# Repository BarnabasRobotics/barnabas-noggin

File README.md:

# barnabas-noggin
Controller board for Barnabas-Bot.  Arduino-Uno compatible board.  

Versions:
 
 Using Nano plug-in board
 - V3: Rev 2C 
 - V3.1: Rev 2D, Rev 2E
 
 No nano plug-in board
 - V4: Rev 3A, 3B 

Changes in Rev2D:
 - Remove 5V regulator
 - Add fuse protection on 5V and 3.3V
 - Add DC Driver Controller
 - Fix silkscreen text

Changes in Rev2E:
 - Silkscreen updates

[AutoDesk Fusion 360 file](https://a360.co/3gs5b8a)

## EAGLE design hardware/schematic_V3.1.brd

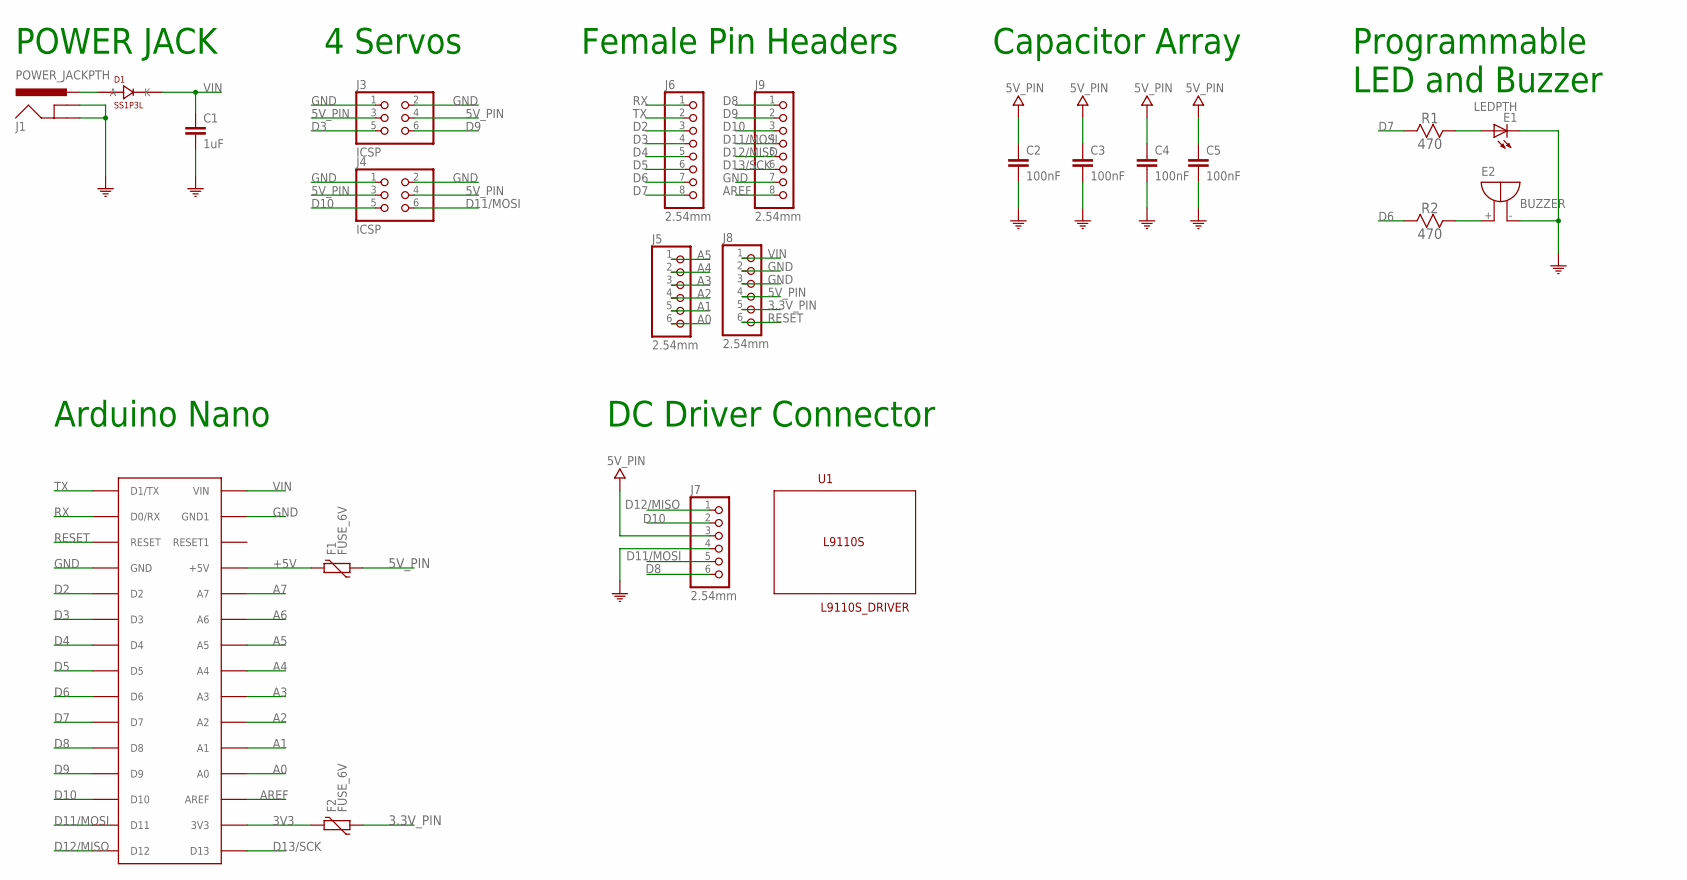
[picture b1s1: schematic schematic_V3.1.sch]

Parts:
C1: 1uF; C0603-ROUND; PARTNO CC0603KRX5R8BB105
C2, C3, C4, C5: 100nF; C0603-ROUND; PARTNO CC0603ZRY5V9BB104
D1: SS1P3L; DIODI_DO220AAL; PARTNO SS1P3L-M3/84A
E1: LEDPTH; LED5MM
E2: BUZZER
F1, F2: FUSE_6V; FUSE_0603; PARTNO MF-FSMF050X-2
J1: POWER_JACKPTH; POWER_JACK_PTH; PARTNO EJ508A
J3, J4: ICSP; CONNECTOR_2X3; PARTNO M20-9980346
J5, J7, J8: 2.54mm; 1X06; PARTNO M20-7820646
J6, J9: 2.54mm; 1X08; PARTNO PPTC081LFBN-RC
R1, R2: 470; RESISTOR_PTH
U1: L9110S_DRIVER
U$1: ARDUINONANO; PDIP-32

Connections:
3.3V_PIN: F2.1, J8.5
3V3: F2.2, U$1.3V3
5V_PIN: C2.1, C3.1, C4.1, C5.1, F1.1, J3.3, J3.4, J4.3, J4.4, J7.3, J8.4
+5V: F1.2, U$1.+5V
A0: J5.6, U$1.A7 (A0)
A1: J5.5, U$1.A6 (A1)
A2: J5.4, U$1.A5 (A2)
A3: J5.3, U$1.A4 (A3)
A4: J5.2, U$1.A3 (A4)
A5: J5.1, U$1.A2 (A5)
A6: U$1.A1 (A6)
A7: U$1.A0 (A7)
AREF: J9.8, U$1.AREF
D2: J6.3, U$1.D2
D3: J3.5, J6.4, U$1.D3
D4: J6.5, U$1.D4
D5: J6.6, U$1.D5
D6: J6.7, R2.1, U$1.D6
D7: J6.8, R1.1, U$1.D7
D8: J7.6, J9.1, U$1.D8
D9: J3.6, J9.2, U$1.D9
D10: J4.5, J7.2, J9.3, U$1.D10
D11/MOSI: J4.6, J7.5, J9.4, U$1.D11
D12/MISO: J7.1, J9.5, U$1.D12
D13/SCK: J9.6, U$1.D13
GND: C1.2, C2.2, C3.2, C4.2, C5.2, E1.K (C), E2.-, J1.GND, J1.GNDBREAK, J3.1, J3.2, J4.1, J4.2, J7.4, J8.2, J8.3, J9.7, U$1.GND, U$1.GND1
unnamed: D1.P$2 (A), J1.PWR
unnamed: E1.A, R1.2
unnamed: E2.+, R2.2
RESET: J8.6, U$1.RESET
RX: J6.1, U$1.D0/RX
TX: J6.2, U$1.D1/TX
VIN: C1.1, D1.P$1 (K), J8.1, U$1.VIN

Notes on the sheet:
Arduino Nano
POWER JACK
4 Servos
Female Pin Headers
Programmable LED and Buzzer
Capacitor Array
DC Driver Connector

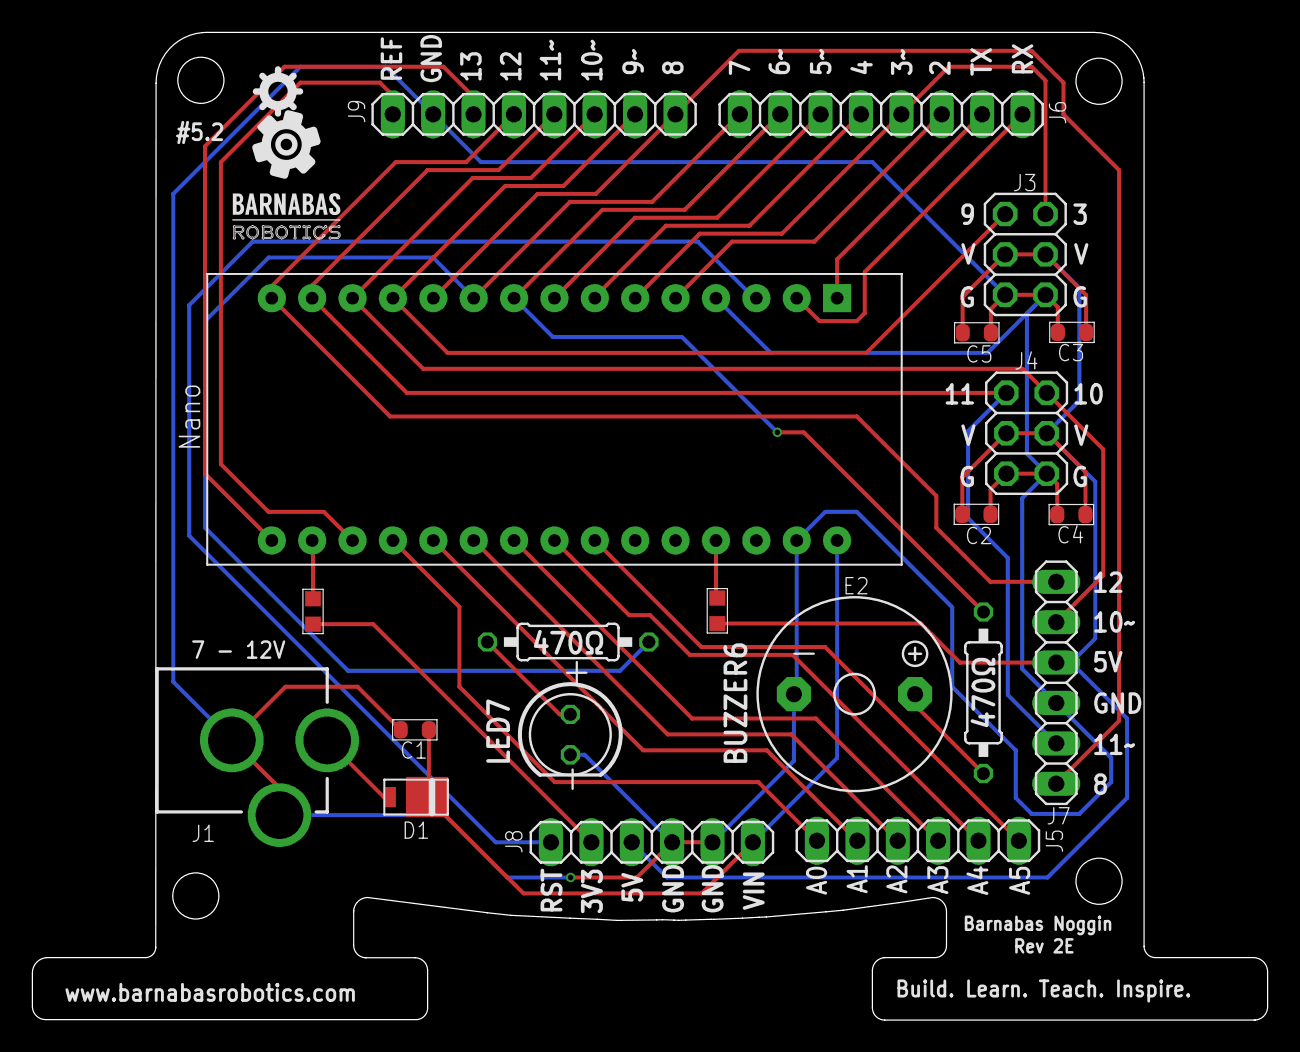
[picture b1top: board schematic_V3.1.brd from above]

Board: 2 copper layers, 77.7 x 62.1 mm, 22 parts (0 on the bottom side), 31 nets.

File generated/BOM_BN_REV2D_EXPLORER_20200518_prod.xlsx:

ITEM | PART ID | VALUE | PACKAGE | SPECIFICATION | QTY | NOTES | BRAND | DIGIKEY PART # | MFG PART # | Notes
1 | C1 | 1uF | 603 | C0603-ROUND | 1 |  | Yageo | 311-1445-2-ND | CC0603KRX5R8BB105
2 | J5, J7, J8 | 2.54mm | Thru-Hole | 2.54 mm female 1 x 6 | 3 |  | Harwin Inc. | 952-1809-ND | M20-7820646
3 | J6, J9 | 2.54mm | Thru-Hole | 2.54 mm female 1 x 8 | 2 |  | Sullins Connector Solutions | S7006-ND | PPTC081LFBN-RC
4 | R1 | 4.7K | Thru-Hole | RESISTOR_PTH | 1 | NO PLACE | * | * | * | NO PLACE
5 | C2, C3, C4, C5 | 100nF | 603 | C0603-ROUND | 4 |  | Yageo | 311-1343-2-ND | CC0603ZRY5V9BB104
6 | R2 | 470 | Thru-Hole | RESISTOR_PTH | 1 | NO PLACE | * | * | * | NO PLACE
7 | Nano | 2.54mm | Thru-Hole | 2.54 mm female 1 x 15 | 2 |  | Sullins Connector Solutions | S7013-ND | ber PPTC151LFBN-RC
8 | E2 | BUZZER | Thru-Hole | 5V Passive buzzer | 1 | NO PLACE | * | * | * | NO PLACE
9 | F1, F2 | FUSE_6V | 603 | FUSE_0603 | 2 |  | Bourns Inc. | MF-FSMF050X-2CT-ND | MF-FSMF050X-2
10 | J3, J4 | 2.54mm | Thru-Hole | 2.54 mm header 2 x 3 | 2 |  | Harwin Inc. | 952-2121-ND | M20-9980346
11 | E1 | 5mm | Thru-Hole | LED5MM | 1 | NO PLACE | * | * | * | NO PLACE
12 | J1 | POWER_JACKPTH | Thru-Hole | POWER_JACK_PTH | 1 |  | MPD (Memory Protection Devices) | EJ508A-ND | EJ508A
13 | D1 | SS1P3L | DO-220AA | DIODI_DO220AAL | 1 |  | Vishay Semiconductor Diodes Division | SS1P3L-M3/84AGITR-ND | SS1P3L-M3/84A
 |  |  |  | Total Thru Hole | 14
 |  |  |  | Total SMD | 8
 |  |  |  | Total parts | 22

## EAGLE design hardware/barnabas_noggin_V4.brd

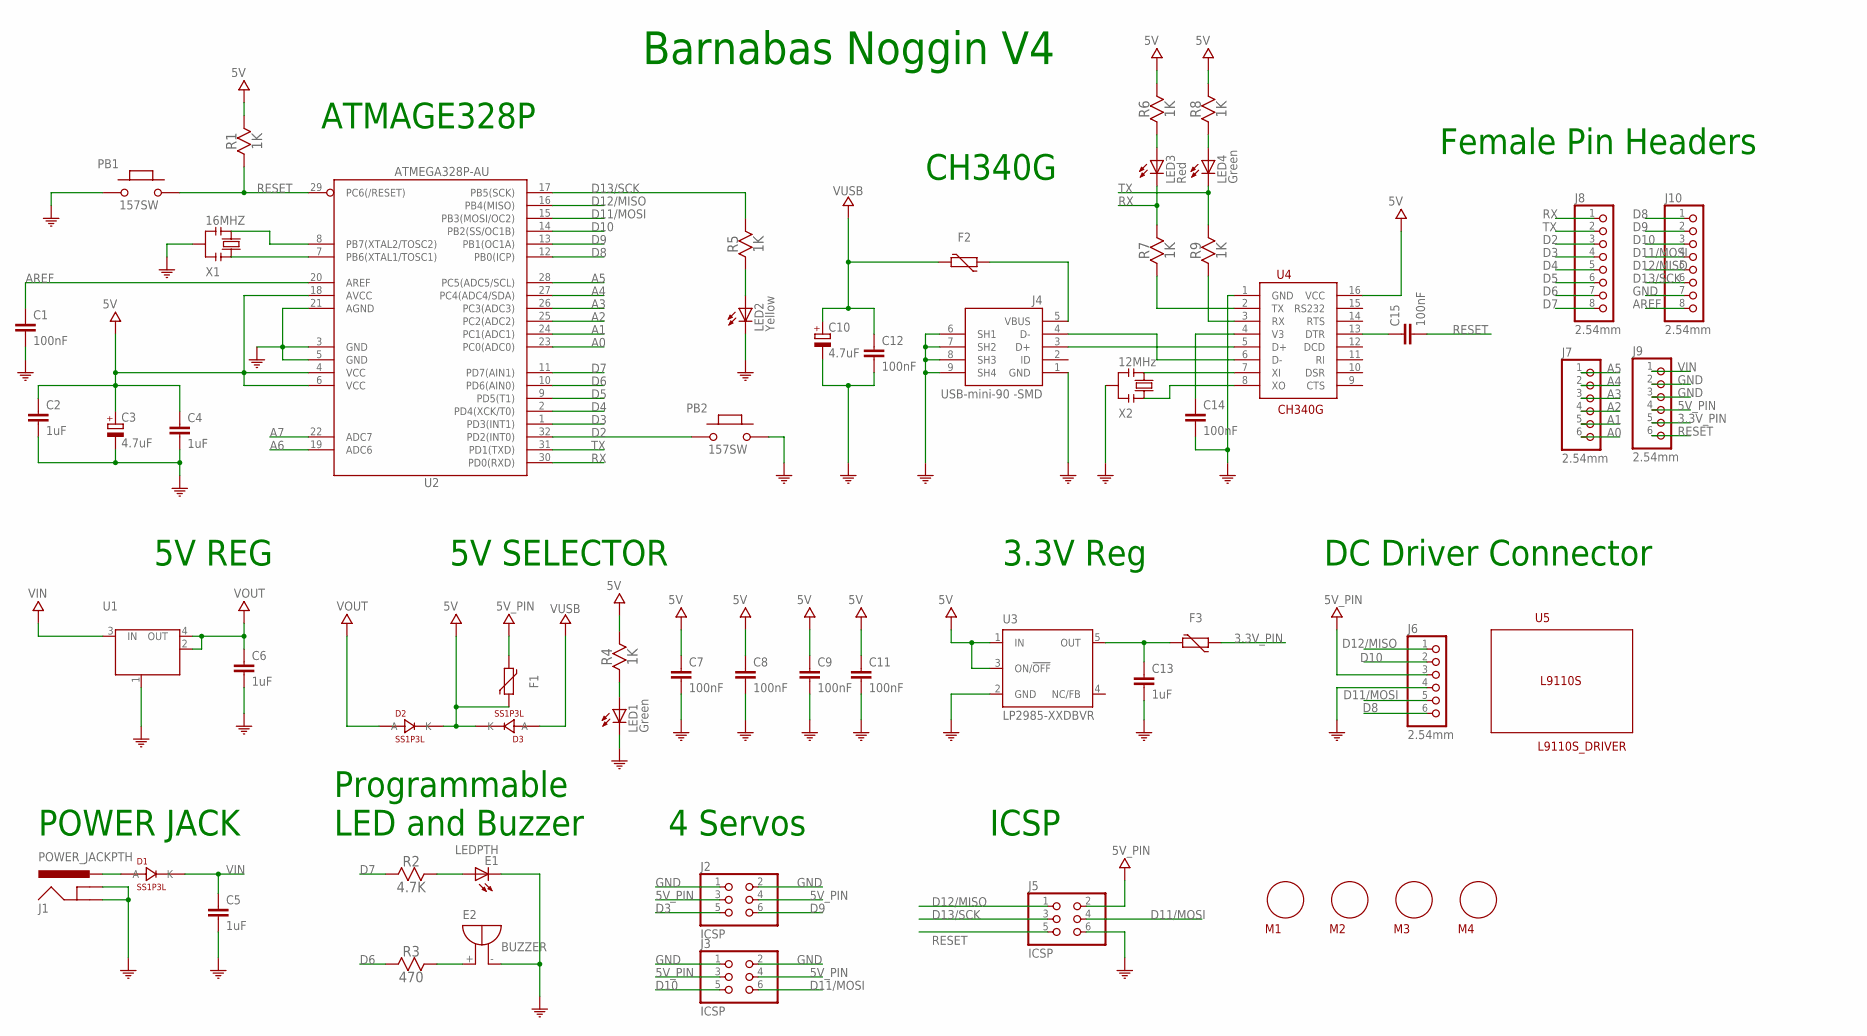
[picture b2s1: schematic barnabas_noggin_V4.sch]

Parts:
C1, C7, C8, C9, C11, C12, C14, C15: 100nF; C0603-ROUND; PARTNO CC0603ZRY5V9BB104
C2, C4, C5, C6, C13: 1uF; C0603-ROUND; PARTNO CC0603KRX5R8BB105
C3, C10: 4.7uF; TAN-A; PARTNO CL31A475KOHNNNE
D1, D2, D3: SS1P3L; DIODI_DO220AAL; PARTNO SS1P3L-M3/84A
E1: LEDPTH; LED5MM
E2: BUZZER
F1, F2, F3: FUSE_6V; FUSE_0603; PARTNO MF-FSMF050X-2
J1: POWER_JACKPTH; POWER_JACK_PTH; PARTNO EJ508A
J2, J3, J5: ICSP; CONNECTOR_2X3; PARTNO M20-9980346
J4: USB-mini-90 -SMD; CONNECTOR_USB_MINI-B; PARTNO UJ2-MBH-1-SMT-TR
J6, J7, J9: 2.54mm; 1X06; PARTNO M20-7820646
J8, J10: 2.54mm; 1X08; PARTNO PPTC081LFBN-RC
LED1, LED4: Green; LED_0805; PARTNO LTST-C171GKT
LED2: Yellow; LED_0805; PARTNO LTST-C171KSKT
LED3: Red; LED_0805; PARTNO LTST-C170KRKT
M1, M2, M3, M4: MOUNT_HOLE
PB1, PB2: 157SW; SWITCHES_SMD_157SW; PARTNO PTS820 J15M SMTR LFS
R1, R4, R5, R6, R7, R8, R9: 1K; R0603; PARTNO RC0603FR-071KL
R2: 4.7K; RESISTOR_PTH
R3: 470; RESISTOR_PTH
U1: LM1117IMPX-5.0; LM1117_SOT223; PARTNO LM1117IMPX-5.0/NOPB
U2: ATMEGA328P-AU; TQFP32-08; PARTNO ATMEGA328P-AU
U3: LP2985-XXDBVR; SOT23-DBV; PARTNO LP2985-33DBVR
U4: CH340G; SOIC16
U5: L9110S_DRIVER
X1: 16MHZ; CRYSTAL; PARTNO CSTNE16M0V530000R0
X2: 12MHz; CRYSTAL; PARTNO CSTNE12M0G550000R0

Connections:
3.3V: C13.1, F3.2, U3.5 (OUT)
3.3V_PIN: F3.1, J9.5
5V: C2.1, C3.1 (+), C4.1, C7.1, C8.1, C9.1, C11.1, D2.P$1 (K), D3.P$1 (K), F1.1, R1.2, R4.2, R6.2, R8.2, U2.4 (VCC), U2.6 (VCC), U2.18 (AVCC), U3.1 (IN), U3.3 (ON/!OFF), U4.16 (VCC)
5V_PIN: F1.2, J2.3, J2.4, J3.3, J3.4, J5.2, J6.3, J9.4
A0: J7.6, U2.23 (PC0(ADC0))
A1: J7.5, U2.24 (PC1(ADC1))
A2: J7.4, U2.25 (PC2(ADC2))
A3: J7.3, U2.26 (PC3(ADC3))
A4: J7.2, U2.27 (PC4(ADC4/SDA))
A5: J7.1, U2.28 (PC5(ADC5/SCL))
A6: U2.19 (ADC6)
A7: U2.22 (ADC7)
AREF: C1.1, J10.8, U2.20 (AREF)
D2: J8.3, PB2.1, U2.32 (PD2(INT0))
D3: J2.5, J8.4, U2.1 (PD3(INT1))
D4: J8.5, U2.2 (PD4(XCK/T0))
D5: J8.6, U2.9 (PD5(T1))
D6: J8.7, R3.1, U2.10 (PD6(AIN0))
D7: J8.8, R2.1, U2.11 (PD7(AIN1))
D8: J6.6, J10.1, U2.12 (PB0(ICP))
D9: J2.6, J10.2, U2.13 (PB1(OC1A))
D10: J3.5, J6.2, J10.3, U2.14 (PB2(SS/OC1B))
D11/MOSI: J3.6, J5.4, J6.5, J10.4, U2.15 (PB3(MOSI/OC2))
D12/MISO: J5.1, J6.1, J10.5, U2.16 (PB4(MISO))
D13/SCK: J5.3, J10.6, R5.2, U2.17 (PB5(SCK))
GND: C1.2, C2.2, C3.2 (-), C4.2, C5.2, C6.2, C7.2, C8.2, C9.2, C10.2 (-), C11.2, C12.2, C13.2, C14.2, E1.K (C), E2.-, J1.GND, J1.GNDBREAK, J2.1, J2.2, J3.1, J3.2, J4.1 (GND), J4.6 (SH1), J4.7 (SH2), J4.8 (SH3), J4.9 (SH4), J5.6, J6.4, J9.2, J9.3, J10.7, LED1.C, LED2.C, PB1.1, PB2.2, U1.1 (GND/ADJ), U2.3 (GND), U2.5 (GND), U2.21 (AGND), U3.2 (GND), U4.1 (GND), X1.2, X2.2
unnamed: U2.8 (PB7(XTAL2/TOSC2)), X1.3
unnamed: U2.7 (PB6(XTAL1/TOSC1)), X1.1
unnamed: LED1.A, R4.1
unnamed: C15.1, U4.13 (DTR)
unnamed: U4.7 (XI), X2.3
unnamed: R7.1, U4.2 (TX)
unnamed: LED3.A, R6.1
unnamed: R9.1, U4.3 (RX)
unnamed: LED4.A, R8.1
unnamed: LED2.A, R5.1
unnamed: C14.1, U4.4 (V3)
unnamed: U4.8 (XO), X2.1
unnamed: J4.3 (D+), U4.5 (D+)
unnamed: J4.4 (D-), U4.6 (D-)
unnamed: D1.P$2 (A), J1.PWR
unnamed: F2.1, J4.5 (VBUS)
unnamed: E1.A, R2.2
unnamed: E2.+, R3.2
RESET: C15.2, J5.5, J9.6, PB1.2, R1.1, U2.29 (PC6(/RESET))
RX: J8.1, LED3.C, R7.2, U2.30 (PD0(RXD))
TX: J8.2, LED4.C, R9.2, U2.31 (PD1(TXD))
VIN: C5.1, D1.P$1 (K), J9.1, U1.3 (IN)
VOUT: C6.1, D2.P$2 (A), U1.2 (OUT), U1.4 (OUT)
VUSB: C10.1 (+), C12.1, D3.P$2 (A), F2.2

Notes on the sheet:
Barnabas Noggin V4
5V REG
ICSP
5V SELECTOR
ATMAGE328P
CH340G
POWER JACK
Programmable LED and Buzzer
4 Servos
Female Pin Headers
DC Driver Connector
3.3V Reg

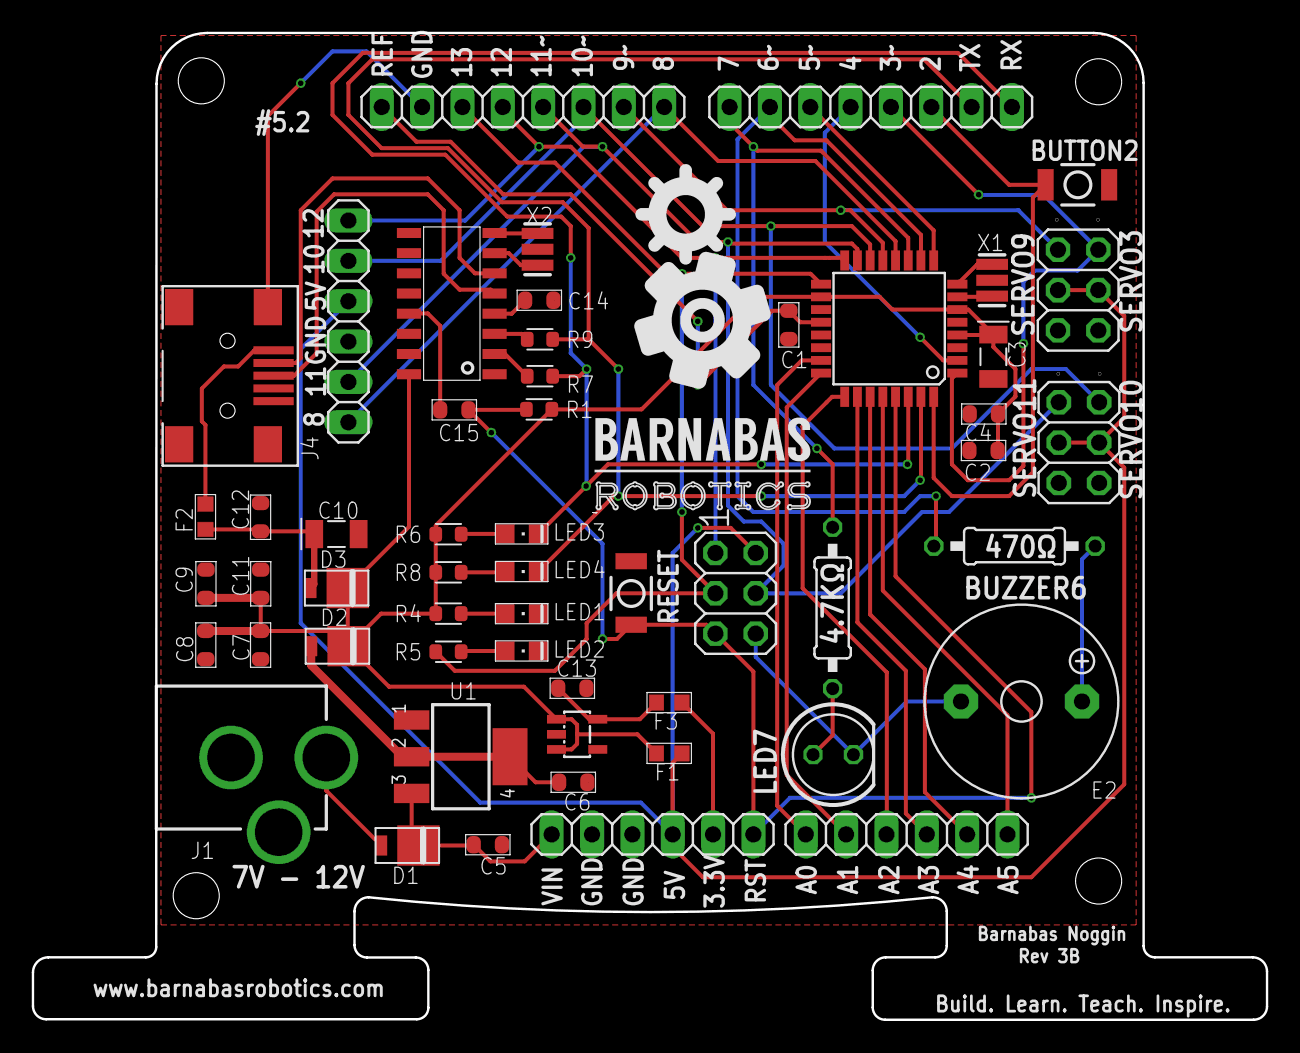
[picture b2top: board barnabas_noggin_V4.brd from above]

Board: 2 copper layers, 77.7 x 62.1 mm, 60 parts (1 on the bottom side), 48 nets.

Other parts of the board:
U$14: BARNABAS_LOGO

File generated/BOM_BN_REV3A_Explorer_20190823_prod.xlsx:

ITEM | PART ID | VALUE | PACKAGE | SPECIFICATION | QTY | NOTES | BRAND | DIGIKEY PART # | MFG PART # | Notes | Other Source
1 | R1, R4, R5, R6, R7, R8, R9 | 1K | 603 | RES SMD 1K OHM 1% 1/10W 0603 | 7 |  | Yageo | 311-1.00KHRTR-ND | RC0603FR-071KL
2 | C2, C4, C5, C6, C13 | 1uF | 603 | CAP CER 1UF 25V X5R 0603 | 5 |  | Yageo | 311-1445-2-ND | CC0603KRX5R8BB105
3 | J6, J7, J9 | 2.54mm | Thru-Hole | CONN RCPT 6POS 0.1 TIN PCB | 3 |  | Harwin Inc. | 952-1809-ND | M20-7820646
4 | J8, J10 | 2.54mm | Thru-Hole | CONN HDR 8POS 0.1 TIN PCB | 2 |  | Sullins Connector Solutions | S7006-ND | PPTC081LFBN-RC
5 | R2 | 4.7K | Thru-Hole | Thru-Hole Resistor | 1 | No Place | * | * | * | No Place
6 | C3, C10 | 4.7uF | 1206 | CAP CER 4.7UF 16V X5R 1206 | 2 |  | Samsung Electro-Mechanics | 1276-3059-2-ND | CL31A475KOHNNNE
7 | X2 | 12MHz | 3-SMD | CER RES 12.0000MHZ 33PF SMD | 1 |  | Murata Electronics North America | 490-17943-2-ND | CSTNE12M0G550000R0
8 | X1 | 16MHZ | 3-SMD | CER RES 16.0000MHZ 15PF SMD | 1 |  | Murata Electronics North America | 490-17948-2-ND | CSTNE16M0V530000R0
9 | C1, C7, C8, C9, C11, C12, C14, C15 | 100nF | 603 | CAP CER 0.1UF 50V Y5V 0603 | 8 |  | Yageo | 311-1343-2-ND | CC0603ZRY5V9BB104
10 | PB1, PB2 | 157SW | * | SWITCH TACTILE SPST-NO 0.05A 12V | 2 |  | C&K | CKN10506TR-ND | PTS820 J15M SMTR LFS
11 | R3 | 470 | Thru-Hole | Thru-Hole Resistor | 1 | No Place | * | * | * | No Place
12 | U2 | ATMEGA328P-32MUR | 32-VQFN (5x5) | IC MCU 8BIT 32KB FLASH 32VQFN | 1 |  | Microchip Technology | ATMEGA328P-MURCT-ND | ATMEGA328P-MUR
13 | E2 | BUZZER | Thru-Hole | 5V Passive Buzzer | 1 | No Place | * | * | * | No Place
14 | U4 | CH340G | * | CH340G | 1 |  | * | * | * |  | https://www.alibaba.com/product-detail/Electronic-Components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
15 | F1, F2, F3 | FUSE_6V | 603 | PTC RESET FUSE 6V 500MA 0603 | 3 |  | Bourns Inc. | MF-FSMF050X-2CT-ND | MF-FSMF050X-2
16 | LED1, LED4 | Green | 805 | LED GREEN CLEAR CHIP SMD | 2 |  | Lite-On Inc. | 160-1423-2-ND | LTST-C171GKT
17 | J2, J3, J5 | ICSP | Thru-Hole | CONN HEADER VERT 6POS 2.54MM | 3 |  | Harwin Inc. | 952-2121-ND | M20-9980346
18 | U5 | L9110S_DRIVER | * | DC Motor Driver | 1 | No Place | * | * | * | No Place
19 | E1 | LEDPTH | Thru-Hole | Thru-Hole 3V LED | 1 | No Place | * | * | * | No Place
20 | U1 | LM1117IMPX-5.0 | SOT-223-4 | IC REG LINEAR 5V 800MA SOT223-4 | 1 |  | Texas Instruments | LM1117IMPX-5.0/NOPBTR-ND | LM1117IMPX-5.0/NOPB
21 | U3 | LP2985-XXDBVR | SOT-23-5 | IC REG LINEAR 3.3V 150MA SOT23-5 | 1 |  | Texas Instruments | 296-18476-2-ND | LP2985-33DBVR
22 | J1 | POWER_JACKPTH | Thru-Hole | CONN PWR JACK 2.1X5.5MM SOLDER | 1 |  | MPD (Memory Protection Devices) | EJ508A-ND | EJ508A
23 | LED3 | Red | 805 | LED RED CLEAR SMD | 1 |  | Lite-On Inc. | 160-1415-2-ND | LTST-C170KRKT
24 | D1, D2, D3 | SS1P3L | DO-220AA | DIODE SCHOTTKY 30V 1.5A DO220AA | 3 |  | Vishay Semiconductor Diodes Division | SS1P3L-M3/84AGITR-ND | SS1P3L-M3/84A
25 | J4 | USB-mini-90 -SMD | * | CONN RCPT USB2.0 MINI B SMD R/A | 1 |  | CUI Inc. | 102-4003-2-ND | UJ2-MBH-1-SMT-TR
26 | LED2 | Yellow | 805 | LED YELLOW CLEAR CHIP SMD | 1 |  | Lite-On Inc. | 160-1428-2-ND | LTST-C171KSKT
 | Total Thru Hole | 13
 | Total SMD | 42
 | Total Parts | 55

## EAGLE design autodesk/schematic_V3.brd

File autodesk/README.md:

### Files here have been created using Eagle 9.6 and Fusion 360 v2.0.8407

Fusion or autodesk seems to create teams upon sign in
Team Files can be found [https://barnabasrobotics.autodesk360.com](https://barnabasrobotics.autodesk360.com/g/all_projects/active)
anyone with the domain email can access

The eagle files have had changes made to the dimensions layer (20)

[Autodesk Hobbyist](https://forums.autodesk.com/t5/fusion-360-support/really-free-for-hobbyist-enthusiast-or-business-that-make-less/td-p/7071441)

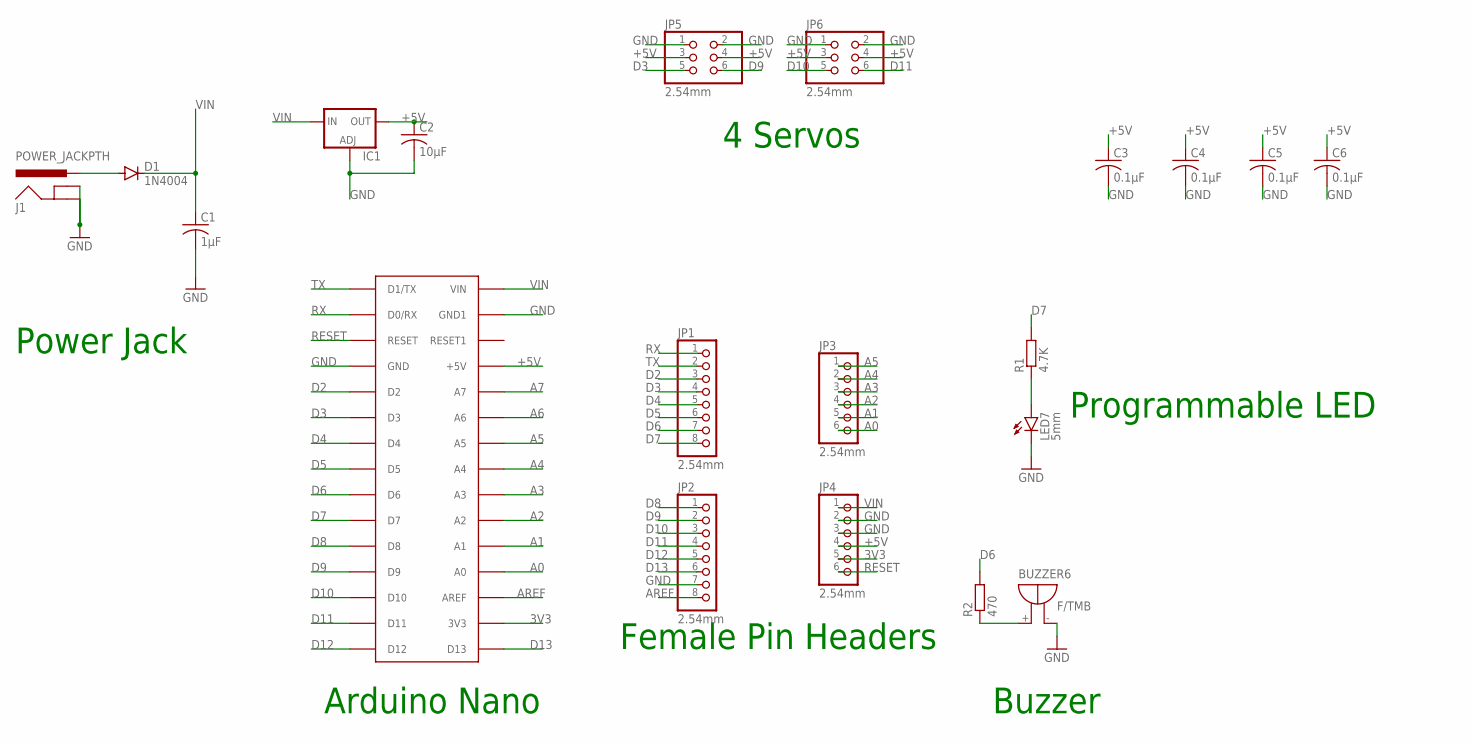
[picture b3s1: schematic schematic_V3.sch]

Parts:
BUZZER6: F/TMB
C1: 1μF; C1206
C2: 10μF; C1206
C3, C4, C5, C6: 0.1μF; C1206
D1: 1N4004; DO41-10
IC1: VR1; SOT223
J1: POWER_JACKPTH; POWER_JACK_PTH
JP1, JP2: 2.54mm; 1X08
JP3, JP4: 2.54mm; 1X06
JP5, JP6: 2.54mm; 2X03
LED7: 5mm; LED5MM
R1: 4.7K; 0207/10
R2: 470; 0207/10
U$1: ARDUINONANO; PDIP-32

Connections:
3V3: JP4.5, U$1.3V3
+5V: C2.1, C3.1, C4.1, C5.1, C6.1, IC1.4 (OUT), JP4.4, JP5.3, JP5.4, JP6.3, JP6.4, U$1.+5V
A0: JP3.6, U$1.A7 (A0)
A1: JP3.5, U$1.A6 (A1)
A2: JP3.4, U$1.A5 (A2)
A3: JP3.3, U$1.A4 (A3)
A4: JP3.2, U$1.A3 (A4)
A5: JP3.1, U$1.A2 (A5)
A6: U$1.A1 (A6)
A7: U$1.A0 (A7)
AREF: JP2.8, U$1.AREF
D2: JP1.3, U$1.D2
D3: JP1.4, JP5.5, U$1.D3
D4: JP1.5, U$1.D4
D5: JP1.6, U$1.D5
D6: JP1.7, R2.2, U$1.D6
D7: JP1.8, R1.2, U$1.D7
D8: JP2.1, U$1.D8
D9: JP2.2, JP5.6, U$1.D9
D10: JP2.3, JP6.5, U$1.D10
D11: JP2.4, JP6.6, U$1.D11
D12: JP2.5, U$1.D12
D13: JP2.6, U$1.D13
GND: BUZZER6.-, C1.2, C2.2, C3.2, C4.2, C5.2, C6.2, IC1.1 (ADJ), J1.GND, J1.GNDBREAK, JP2.7, JP4.2, JP4.3, JP5.1, JP5.2, JP6.1, JP6.2, LED7.K (C), U$1.GND, U$1.GND1
unnamed: LED7.A, R1.1
unnamed: D1.A, J1.PWR
unnamed: BUZZER6.+, R2.1
RESET: JP4.6, U$1.RESET
RX: JP1.1, U$1.D0/RX
TX: JP1.2, U$1.D1/TX
VIN: C1.1, D1.C, IC1.3 (IN), JP4.1, U$1.VIN

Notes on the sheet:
Power Jack
Arduino Nano
4 Servos
Female Pin Headers
Programmable LED
Buzzer

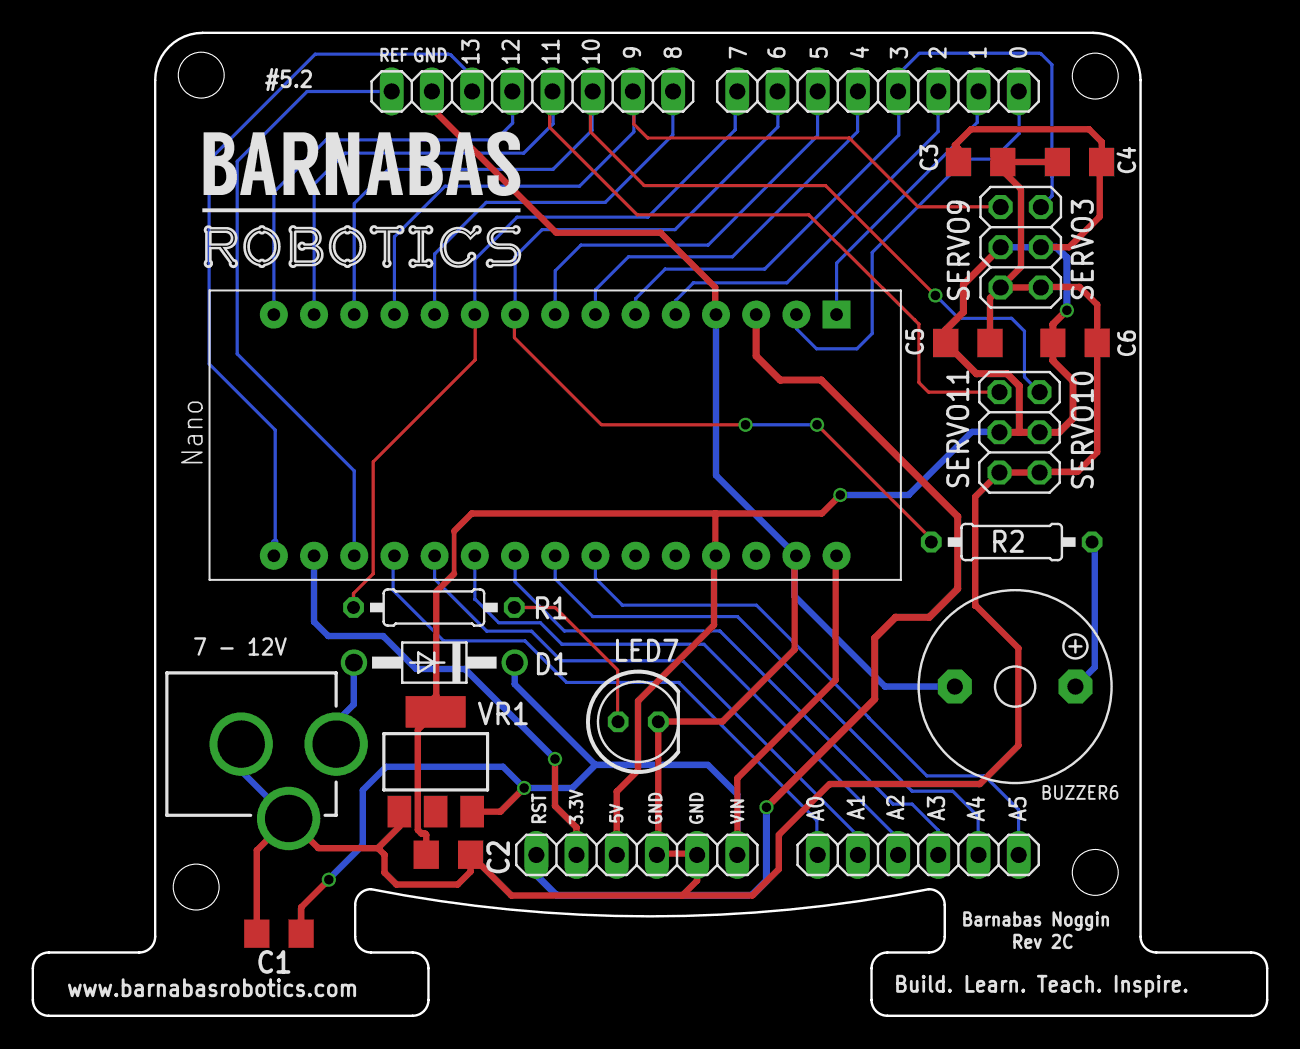
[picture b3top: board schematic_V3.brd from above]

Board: 2 copper layers, 78.0 x 62.1 mm, 20 parts (0 on the bottom side), 29 nets.

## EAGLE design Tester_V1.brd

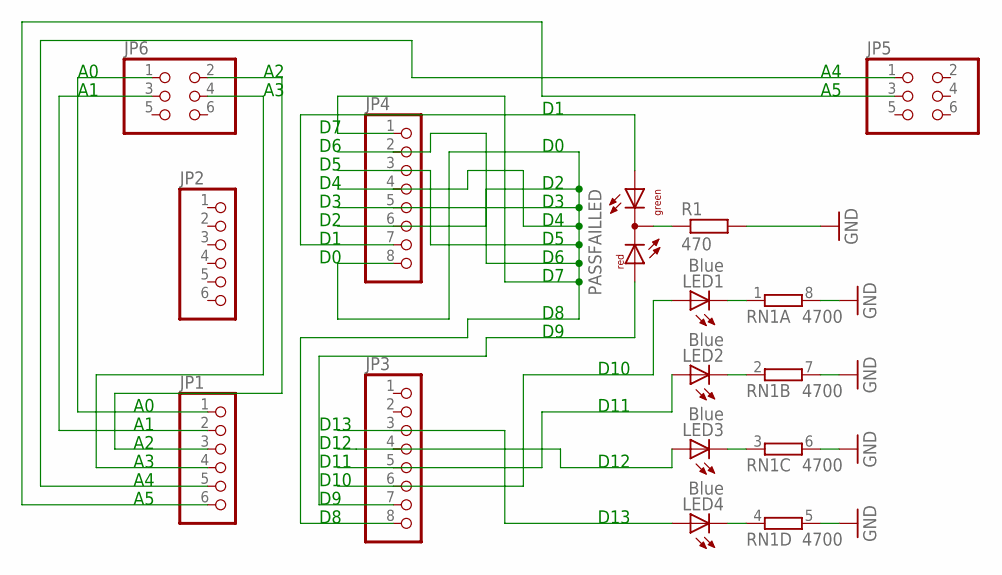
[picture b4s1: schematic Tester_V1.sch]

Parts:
JP1, JP2: PINHD-1X6; 1X06
JP3, JP4: PINHD-1X8; 1X08
JP5, JP6: PINHD-2X3; 2X03
LED1, LED2, LED3, LED4: Blue; SMARTLED-TTW
PASSFAILLED: DUOLED-RG-C; DUOLED-C-5MM
R1: 470; R0805
RN1: 4700; 0603-ARV

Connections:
GND: R1.2, RN1.5 (2), RN1.6 (2), RN1.7 (2), RN1.8 (2)
unnamed: JP3.4, LED3.A@1 (A)
unnamed: JP3.5, LED2.A@1 (A)
unnamed: JP3.6, LED1.A@1 (A)
unnamed: JP4.7, PASSFAILLED.AX (AG)
unnamed: JP1.1, JP6.1
unnamed: JP1.2, JP6.3
unnamed: JP3.8, JP4.1, JP4.2, JP4.3, JP4.4, JP4.5, JP4.6, JP4.8
unnamed: JP3.7, PASSFAILLED.AR
unnamed: JP1.3, JP6.2
unnamed: JP1.4, JP6.4
unnamed: LED4.C@1 (C), RN1.4 (1)
unnamed: JP1.5, JP5.1
unnamed: JP1.6, JP5.3
unnamed: PASSFAILLED.C, R1.1
unnamed: JP3.3, LED4.A@1 (A)
unnamed: LED1.C@1 (C), RN1.1
unnamed: LED3.C@1 (C), RN1.3 (1)
unnamed: LED2.C@1 (C), RN1.2 (1)

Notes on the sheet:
D10
D11
D12
D13

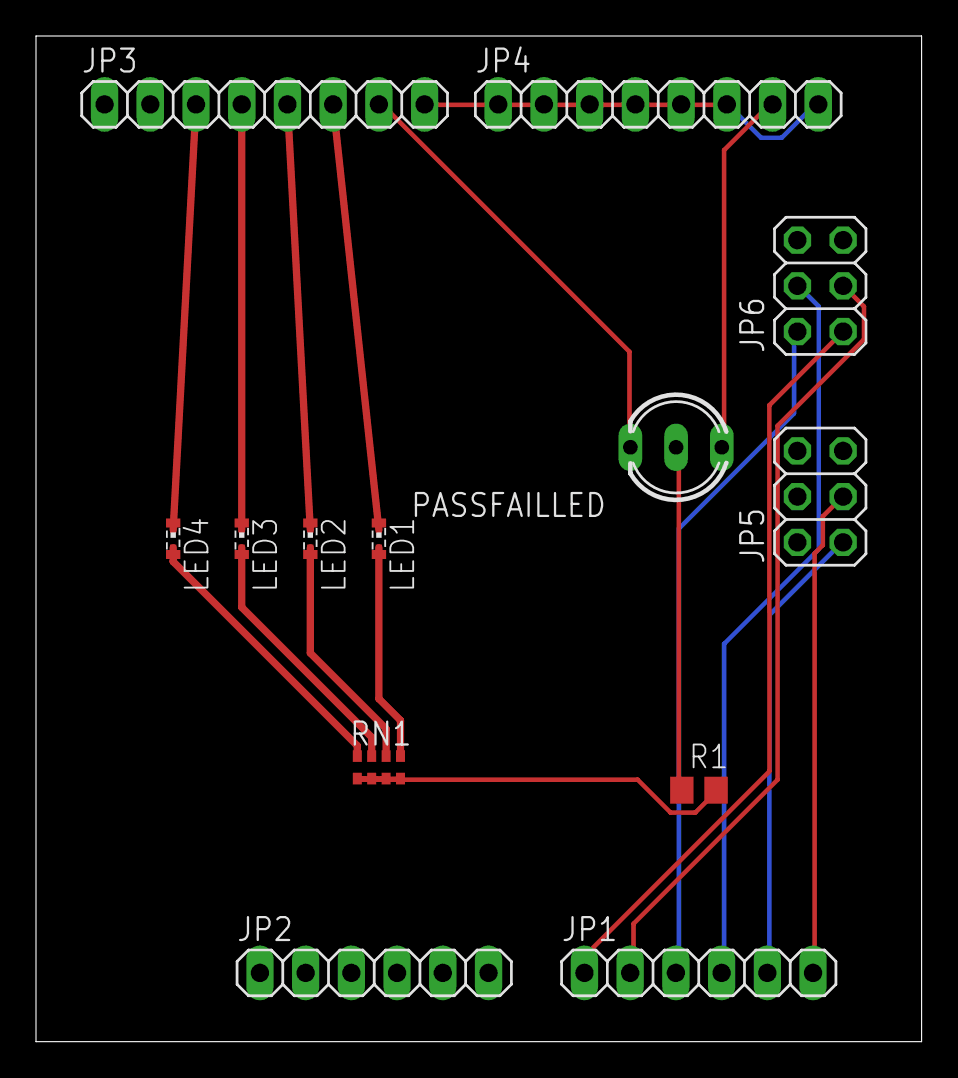
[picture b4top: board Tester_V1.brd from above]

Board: 2 copper layers, 49.2 x 55.9 mm, 13 parts (0 on the bottom side), 19 nets.

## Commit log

2016-07-13 Create license
2016-07-13 version two
2016-07-13 Vincent added mounting holes
2017-02-11 3rd revision of noggin - Vincent Kok
    Moved all components to top side of the board
2017-04-05 Ctrl KiCad Schematic RevD1
2017-08-31 outline of pcb -- dxf files
2018-06-19 Add files via upload
    5VS and +5V rails merged
2018-06-20 Create rev 1B
2018-06-20 Rev C from Vincent
2018-06-26 Add files via upload
    Connected 5VS and +5V rails. Minor cleanup of warnings prompted in Eagle
2018-07-09 Thickened +5V traces
2018-07-09 Designated VR1 as NO PLACE
2018-07-12 Up to date ger/drill files
2018-07-22 silkscreen corrected. 2C displayed as version.
2018-07-23 Now displays rev_2C as version no.
2019-07-31 Finished schematic for V4 board. Added corresponding library and part database. Board not routed yet.
2019-08-08 Updated V4 schematics.
2019-08-08 Added V4 board schematics.
2019-08-12 Added 3.3V regulator.
2019-08-16 complete routing
2019-08-19 Upload latest schematics.
2019-08-19 Update board surface text.
2019-08-20 update documentation print.
2019-08-23 Modify silkscreen text. Update logo pattern.
2019-08-23 Update documentation print and schematics. Upload BOM file.
2019-08-23 modify logo and dc driver package.
2019-08-23 modify text.
2019-08-23 update board and schematics files.
2019-11-08 Replaced with new ATMEGA328 chip and modified PWM pins
2019-11-15 Replaced fuses. Added pull-up resistor for pin 2.
2019-12-26 Fixed some silk screen text.
2019-12-27 Uploaded new schematic PDF, documentation print, silkscreen from OSH, BOM and gerbers.
2020-01-16 Removed pin2 pullup resistor. Uploaded and updated files for Rev3B.
2020-05-07 Modified V3 Board as new V3.1 Board and readme file
2020-05-13 from fusion 360
2020-05-15 Finished routing and change the logo
2020-05-18 Moved the logo and generated BOM
2020-05-26 add link to fusion 360 file
2020-05-26 autodesk files
2020-06-08 modified the screensilk
2020-06-08 change 4.7K resistor to 470 resistor
2020-06-10 Tried out assigning 3D models
2020-06-11 Assigned more 3D models
2020-06-11 Update library for V4 board
2020-06-15 Updated Rev2D to Rev2E. Fixed screensilk and uploaded new BOM and gerbers
2020-06-22 add .obj file of Rev2E
2020-06-30 Replace 3D models for resistors, LED, and Buzzer
